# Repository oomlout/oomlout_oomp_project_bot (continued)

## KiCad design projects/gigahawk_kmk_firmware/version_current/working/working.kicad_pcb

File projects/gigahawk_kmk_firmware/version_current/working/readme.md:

# kmk_firmware by Gigahawk  
This is a harvested standardized copy of a project from github.  
The original project can be found at:  
https://github.com/Gigahawk/kmk_firmware  
Please consult that link for additional, details, files, and license information.  
Note: It was auto harvested and if the original repo had more than one board file or anything out of the ordinary the files here are likely not representative.

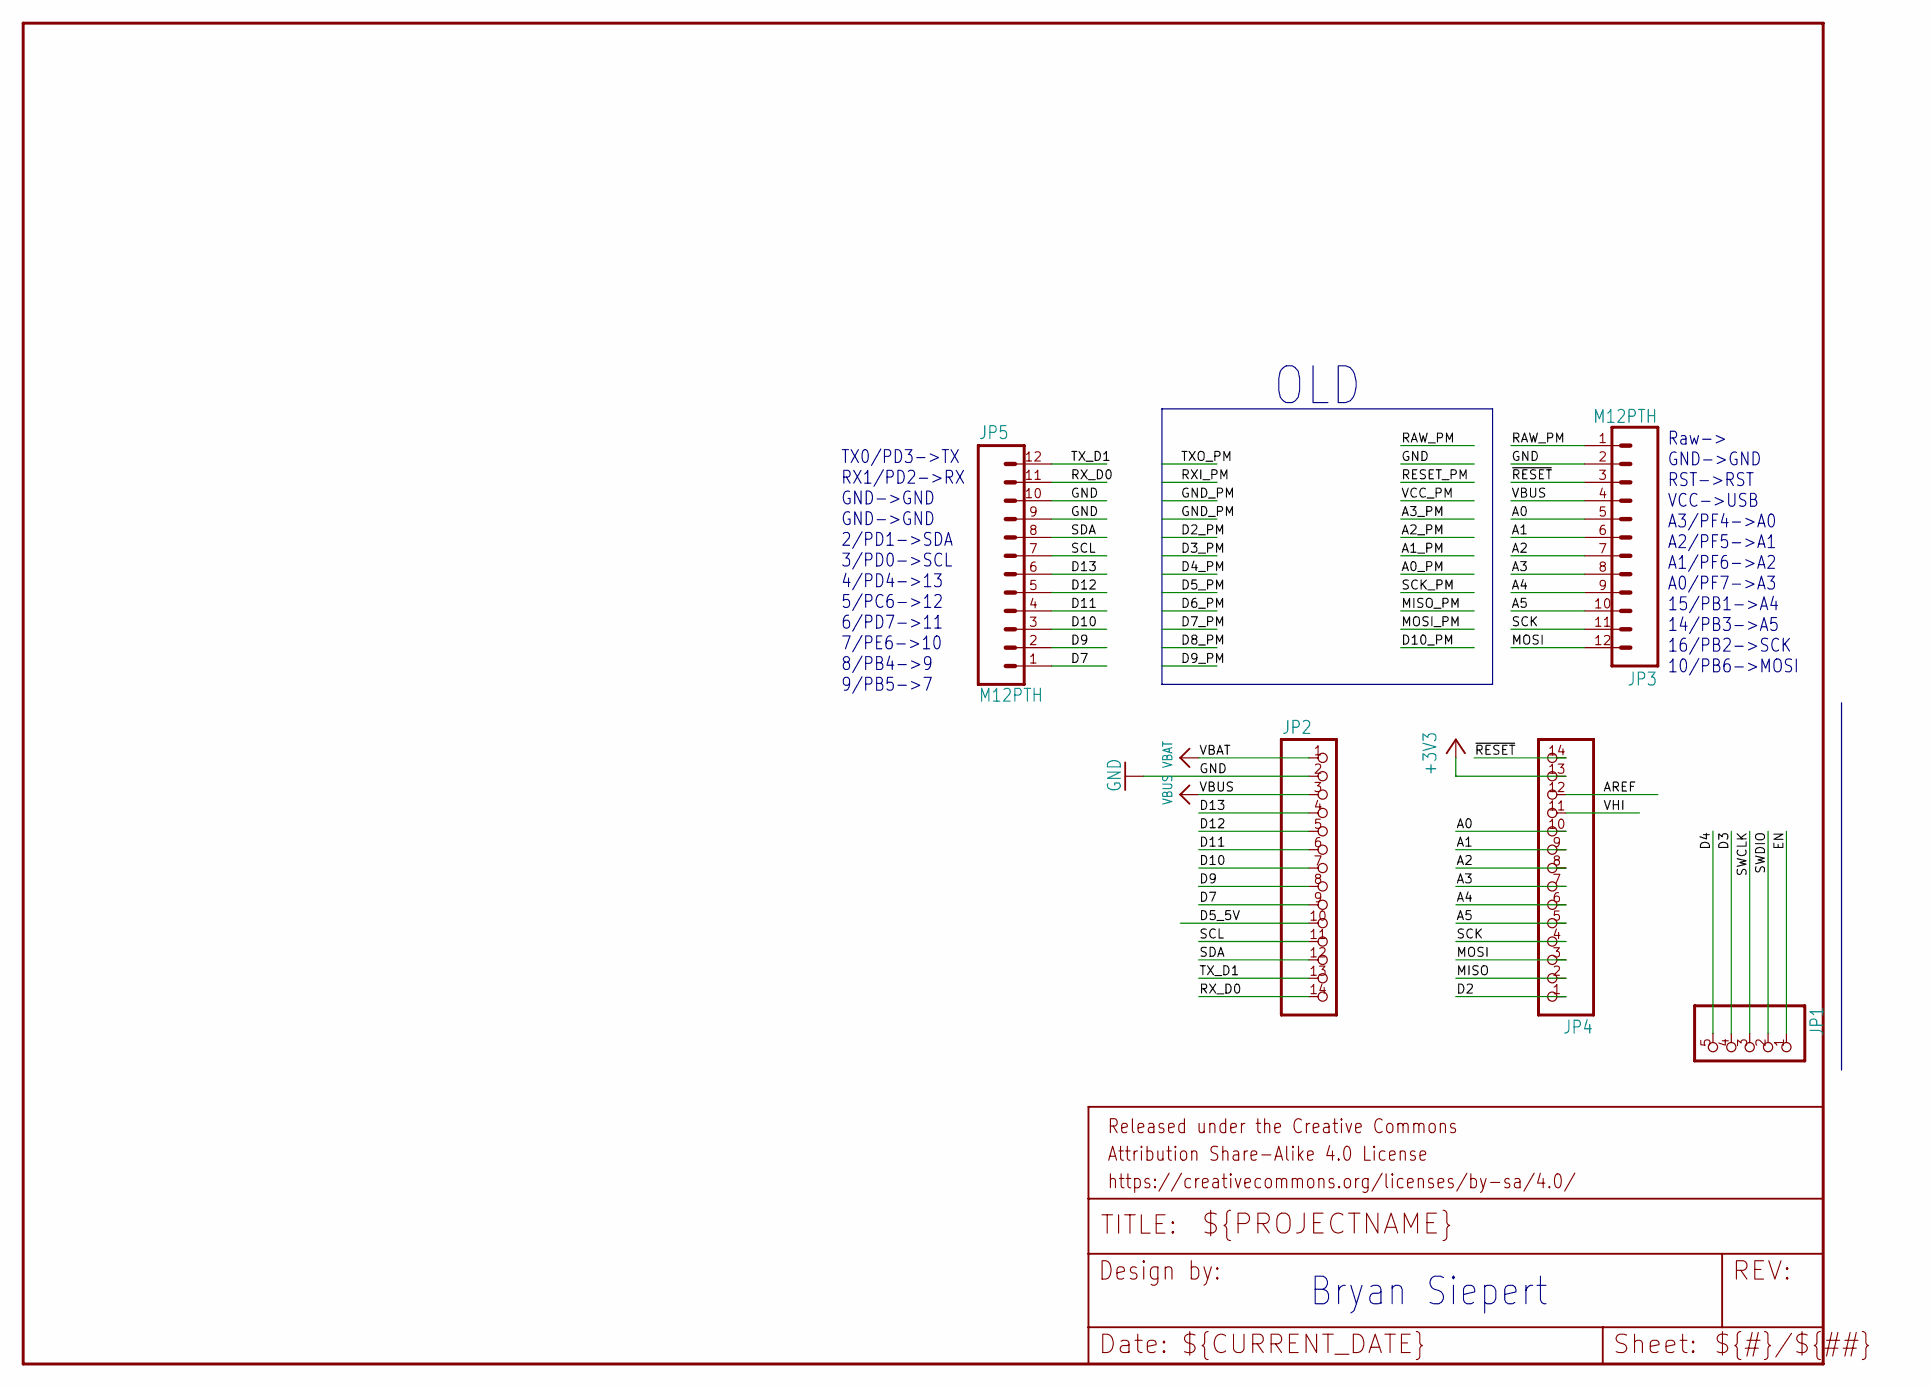
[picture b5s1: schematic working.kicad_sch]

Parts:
FRAME2: FRAME-LETTER; CREATIVE_COMMONS
JP1: HEADER-1X570MIL; 1X05_ROUND_70
JP2, JP4: HEADER-1X14; 1X14_ROUND70
JP3, JP5: M12PTH; 1X12

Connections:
+3V3: JP4.13
A0: JP3.5, JP4.10
A1: JP3.6, JP4.9
A2: JP3.7, JP4.8
A3: JP3.8, JP4.7
A4: JP3.9, JP4.6
A5: JP3.10, JP4.5
AREF: JP4.12
D2: JP4.1
D3: JP1.4
D4: JP1.5
D5_5V: JP2.10
D7: JP2.9, JP5.1
D9: JP2.8, JP5.2
D10: JP2.7, JP5.3
D11: JP2.6, JP5.4
D12: JP2.5, JP5.5
D13: JP2.4, JP5.6
EN: JP1.1
GND: JP2.2, JP3.2, JP5.9, JP5.10
MISO: JP4.2
MOSI: JP3.12, JP4.3
RAW_PM: JP3.1
RX_D0: JP2.14, JP5.11
SCK: JP3.11, JP4.4
SCL: JP2.11, JP5.7
SDA: JP2.12, JP5.8
SWCLK: JP1.3
SWDIO: JP1.2
TX_D1: JP2.13, JP5.12
VBAT: JP2.1
VBUS: JP2.3, JP3.4
VHI: JP4.11
~RESET: JP3.3, JP4.14

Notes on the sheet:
TX0/PD3->TX RX1/PD2->RX GND->GND GND->GND 2/PD1->SDA 3/PD0->SCL 4/PD4->13 5/PC6->12 6/PD7->11 7/PE6->10 8/PB4->9 9/PB5->7
Raw-> GND->GND RST->RST VCC->USB A3/PF4->A0 A2/PF5->A1 A1/PF6->A2 A0/PF7->A3 15/PB1->A4 14/PB3->A5 16/PB2->SCK 10/PB6->MOSI
OLD
Bryan Siepert

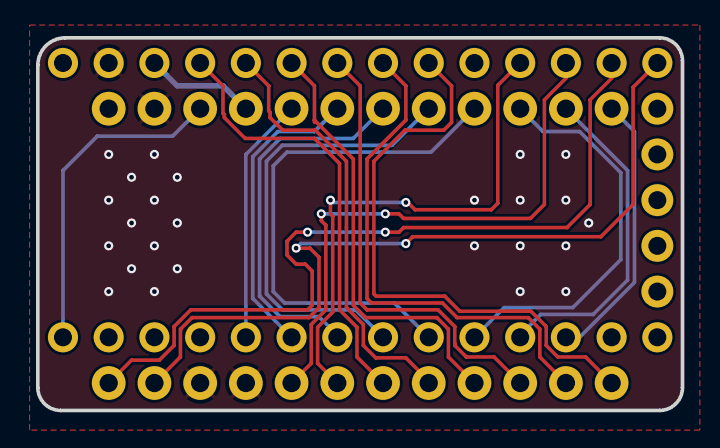
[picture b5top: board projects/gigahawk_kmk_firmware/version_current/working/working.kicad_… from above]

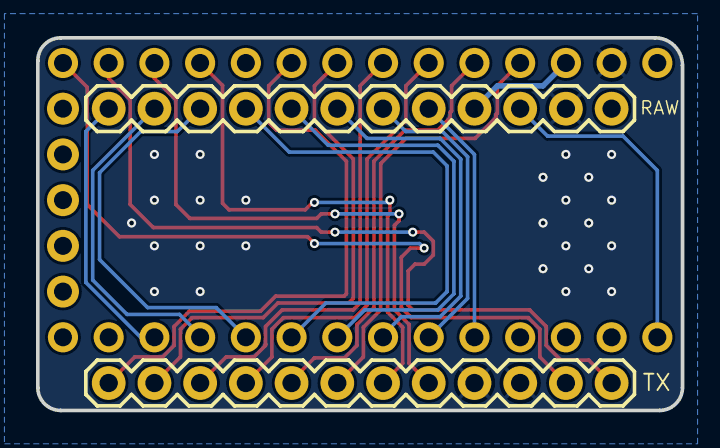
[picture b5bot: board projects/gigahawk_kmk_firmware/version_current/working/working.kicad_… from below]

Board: 4 copper layers, 35.8 x 20.7 mm, 6 parts (2 on the bottom side), 21 nets.

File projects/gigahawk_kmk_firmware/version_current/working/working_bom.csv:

"Id";"Designator";"Footprint";"Quantity";"Designation";"Supplier and ref";
1;"JP1";"1X05_ROUND_70";1;"";;;
2;"JP4,JP2";"1X14_ROUND70";2;"";;;
3;"FRAME2";"CREATIVE_COMMONS";1;"FRAME-LETTER";;;
4;"JP5,JP3";"1X12";2;"";;;

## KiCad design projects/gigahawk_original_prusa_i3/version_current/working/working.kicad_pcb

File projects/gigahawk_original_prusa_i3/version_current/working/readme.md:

# Original-Prusa-i3 by Gigahawk  
This is a harvested standardized copy of a project from github.  
The original project can be found at:  
https://github.com/Gigahawk/Original-Prusa-i3  
Please consult that link for additional, details, files, and license information.  
Note: It was auto harvested and if the original repo had more than one board file or anything out of the ordinary the files here are likely not representative.

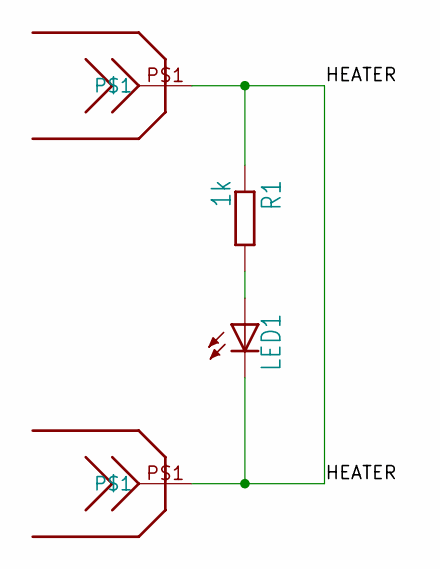
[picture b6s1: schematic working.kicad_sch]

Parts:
LED1: LEDCHIPLED_0805; CHIPLED_0805
R1: 1k; M0805
U$1, U$2: FASTONSMD

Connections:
HEATER: LED1.C, R1.1, U$1.P$1, U$2.P$1
unnamed: LED1.A, R1.2

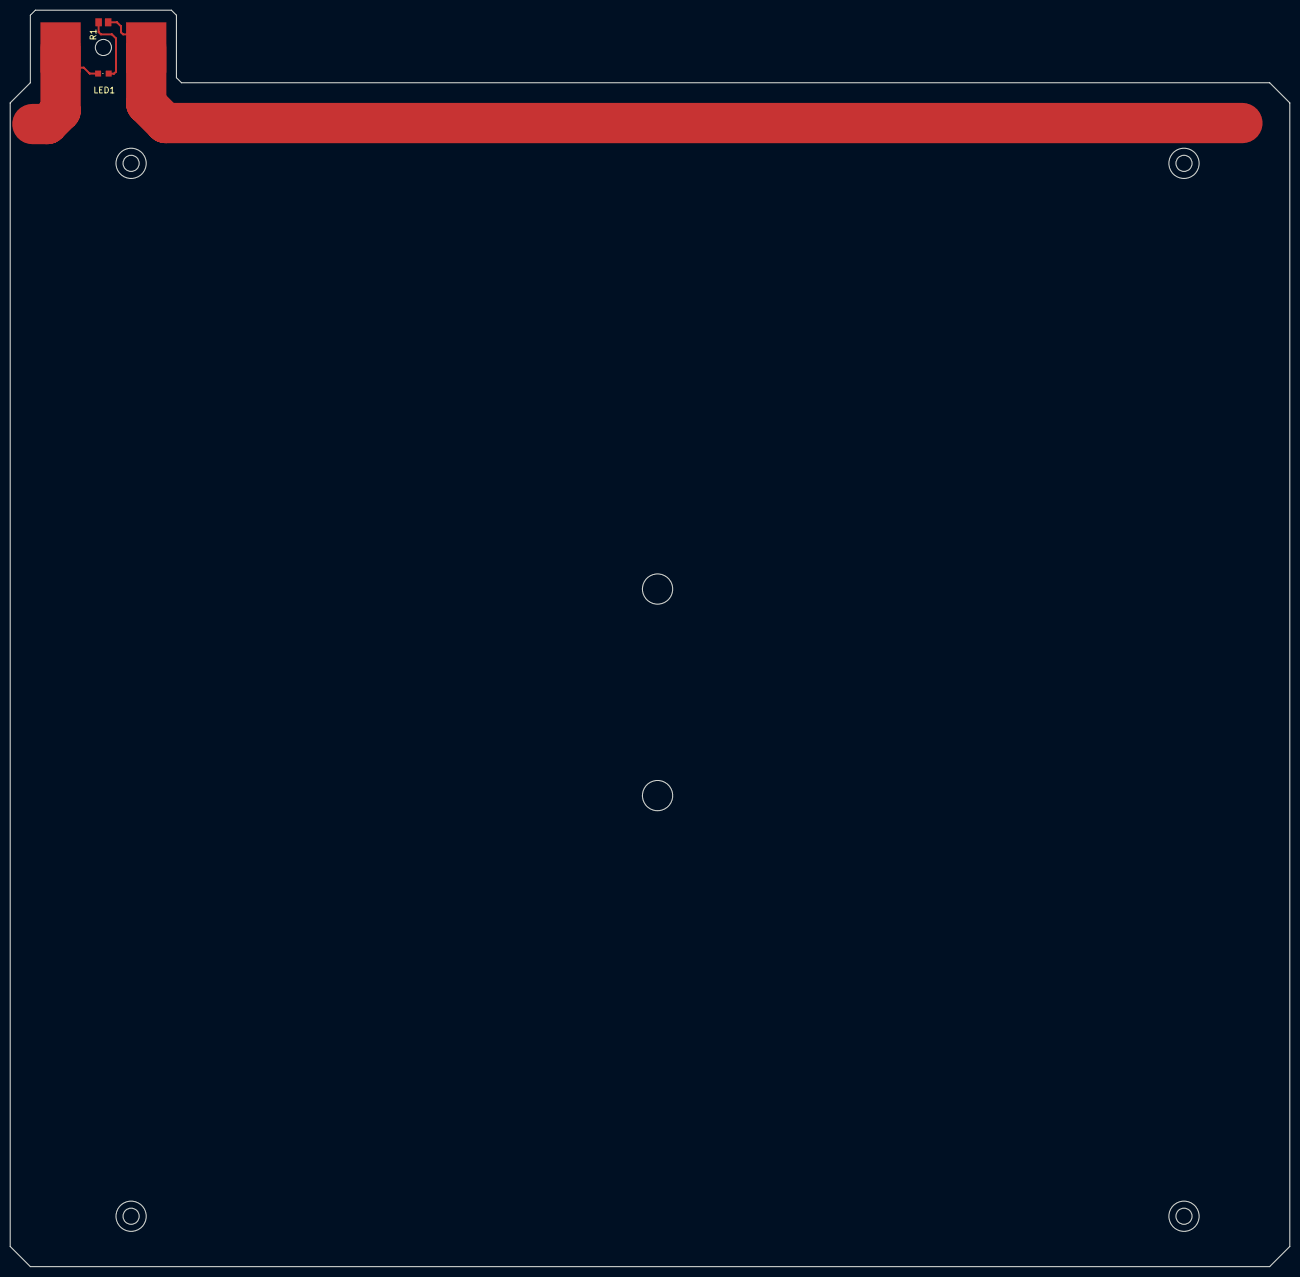
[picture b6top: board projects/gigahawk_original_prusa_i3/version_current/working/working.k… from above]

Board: 6 copper layers, 254.0 x 249.4 mm, 15 parts (0 on the bottom side), 2 nets.

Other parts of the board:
@HOLE0, @HOLE1, @HOLE2, @HOLE3, @HOLE4, @HOLE5, @HOLE6, @HOLE7, @HOLE8, @HOLE9, @HOLE10: (no value)
